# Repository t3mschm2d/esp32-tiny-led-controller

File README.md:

# ESP32-Tiny-LED-Controller

## Overview

The main goal of this project is to develop an OpenHardware board for controlling digital LED strips. The control shall be done via [Homeassistant](https://www.home-assistant.io) and [esphome](https://esphome.io).The PCB is based around an [ESP32-U4WDH](https://www.espressif.com/sites/default/files/documentation/esp32_datasheet_en.pdf) microcontroller and includes the following features: 

- 2,4GHz antenna for WLAN / Bluetooth 
- 5 pin screw terminal for external power and the LED-strip 
- USB-C connector
- USB-to-UART converter
- JST PH-S4B for connecting external sensors 

## ToDos

This PCB is a work in progress. The latest design is not tested and verified.

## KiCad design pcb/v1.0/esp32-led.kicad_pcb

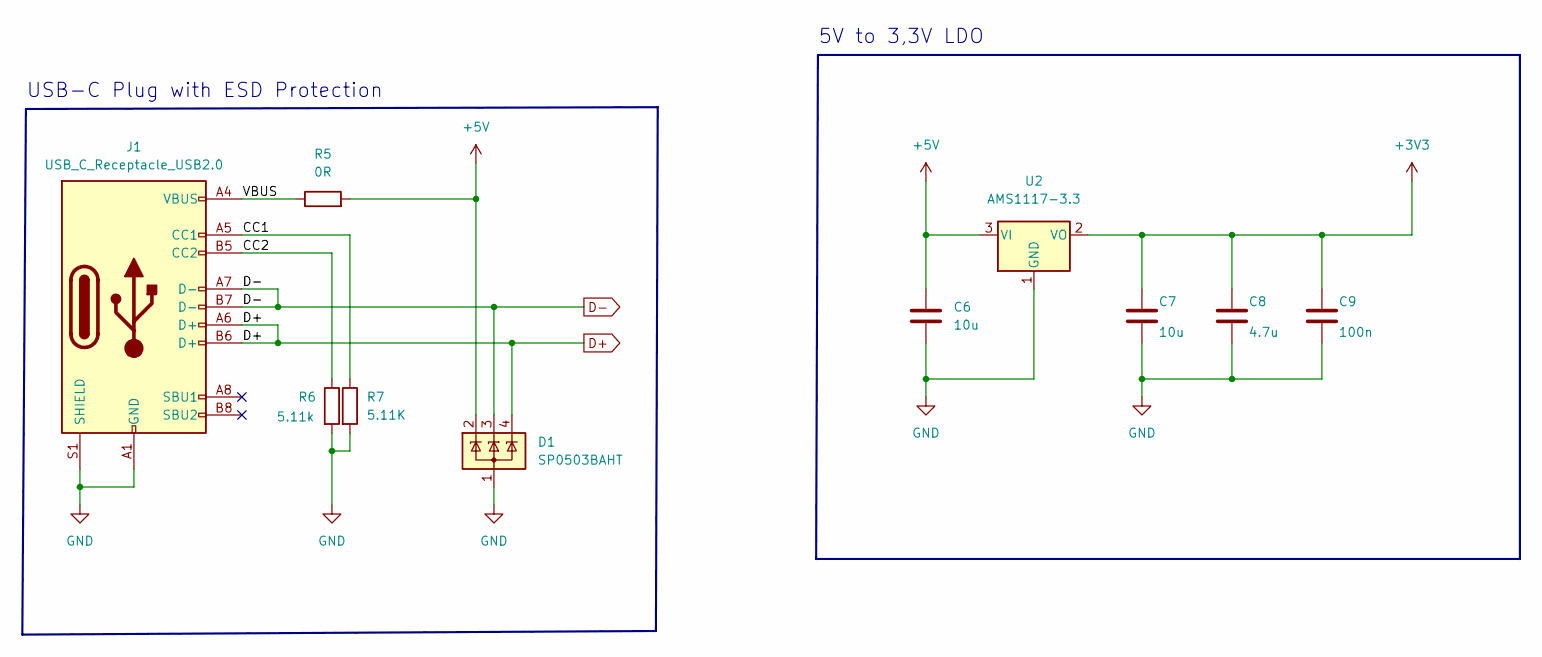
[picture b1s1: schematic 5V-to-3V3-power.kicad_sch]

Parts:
C6: 10u; C_0603_1608Metric
C7: 10u; C_0402_1005Metric
C8: 4.7u; C_0402_1005Metric
C9: 100n; C_0402_1005Metric
D1: SP0503BAHT; SOT-143
J1: USB_C_Receptacle_USB2.0; USB_C_Receptacle_JAE_DX07S016JA1R1500
R5: 0R; R_0805_2012Metric_Pad1.20x1.40mm_HandSolder
R6: 5.11k; R_0402_1005Metric
R7: 5.11K; R_0402_1005Metric
U2: AMS1117-3.3; SOT-223-3_TabPin2

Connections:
+3V3: C7.1, C8.1, C9.1, U2.2 (VO); also elsewhere on the board
+5V: C6.1, D1.2 (K), R5.2, U2.3 (VI); also elsewhere on the board
/5V to 3.3V Power/CC1: J1.A5 (CC1), R7.1
/5V to 3.3V Power/CC2: J1.B5 (CC2), R6.1
/5V to 3.3V Power/VBUS: J1.A4 (VBUS), J1.A9 (VBUS), J1.B4 (VBUS), J1.B9 (VBUS), R5.1
D+: D1.4 (K), J1.A6 (D+), J1.B6 (D+); also elsewhere on the board
D-: D1.3 (K), J1.A7 (D-), J1.B7 (D-); also elsewhere on the board
GND: C6.2, C7.2, C8.2, C9.2, D1.1 (A), J1.A1 (GND), J1.A12 (GND), J1.B1 (GND), J1.B12 (GND), J1.S1 (SHIELD), R6.2, R7.2, U2.1 (GND); also elsewhere on the board

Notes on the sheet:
5V to 3,3V LDO
USB-C Plug with ESD Protection

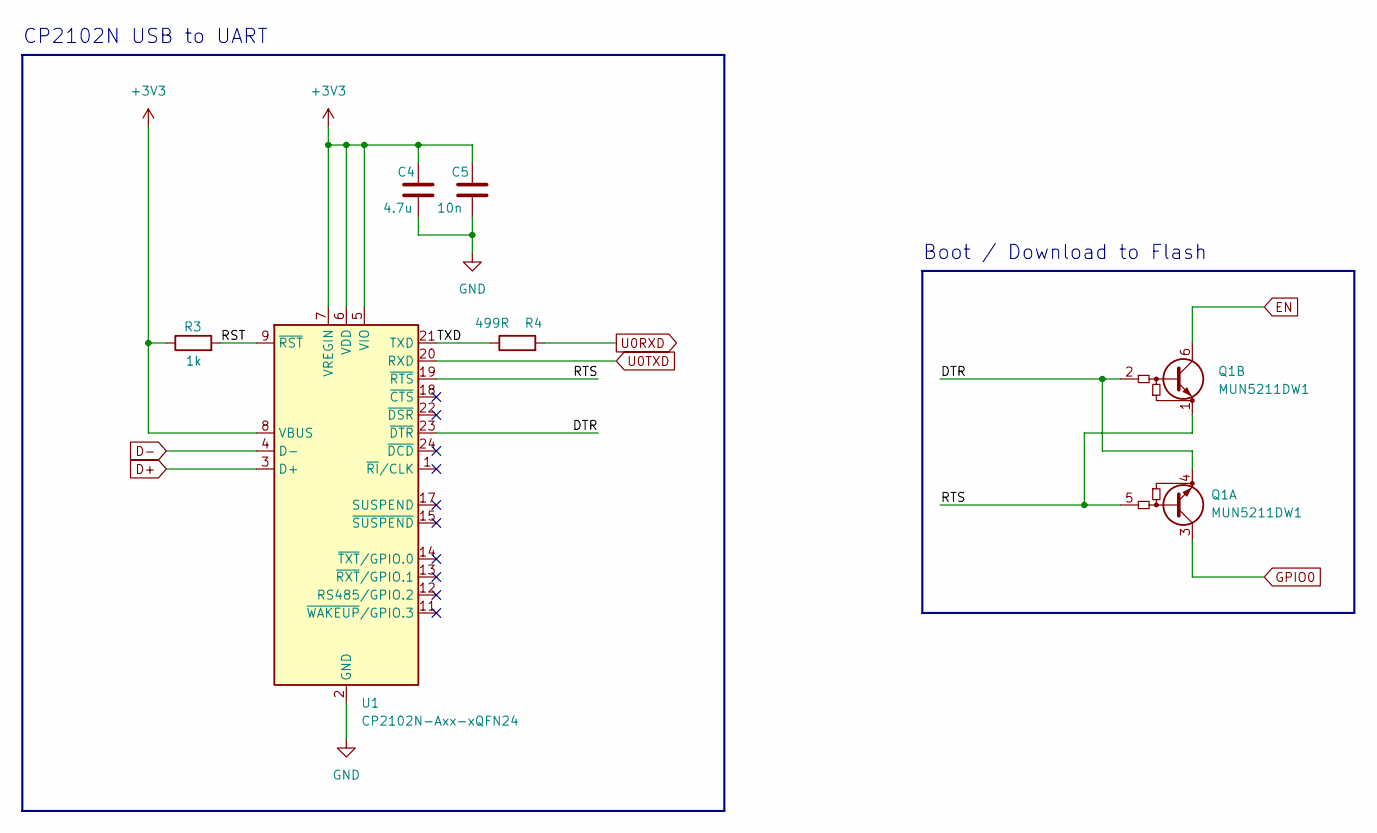
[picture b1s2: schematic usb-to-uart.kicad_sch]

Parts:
C4: 4.7u; C_0402_1005Metric
C5: 10n; C_0402_1005Metric
Q1: MUN5211DW1; SOT-363_SC-70-6
R3: 1k; R_0402_1005Metric
R4: 499R; R_0402_1005Metric
U1: CP2102N-Axx-xQFN24; QFN-24-1EP_4x4mm_P0.5mm_EP2.6x2.6mm

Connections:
+3V3: C4.1, C5.1, R3.1, U1.5 (VIO), U1.6 (VDD), U1.7 (VREGIN), U1.8 (VBUS); also elsewhere on the board
/USB to UART /DTR: Q1.2 (B2), Q1.4 (E1), U1.23 (~DTR)
/USB to UART /RST: R3.2, U1.9 (~RST)
/USB to UART /RTS: Q1.1 (E2), Q1.5 (B1), U1.19 (~RTS)
/USB to UART /TXD: R4.1, U1.21 (TXD)
D+: U1.3 (D+); also elsewhere on the board
D-: U1.4 (D-); also elsewhere on the board
EN: Q1.6 (C2); also elsewhere on the board
GND: C4.2, C5.2, U1.2 (GND), U1.25 (GND); also elsewhere on the board
GPIO0: Q1.3 (C1); also elsewhere on the board
U0RXD: R4.2; also elsewhere on the board
U0TXD: U1.20 (RXD); also elsewhere on the board

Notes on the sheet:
CP2102N USB to UART
Boot / Download to Flash

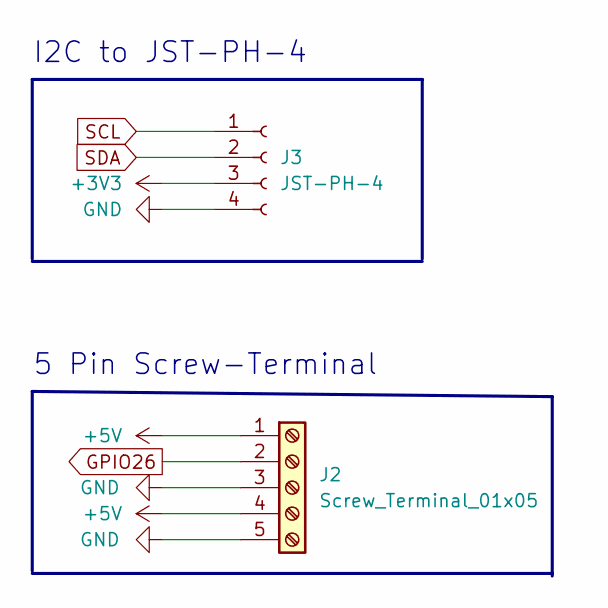
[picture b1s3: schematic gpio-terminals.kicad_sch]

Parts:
J2: Screw_Terminal_01x05; TerminalBlock_Phoenix_MKDS-1,5-5-5.08_1x05_P5.08mm_Horizont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
J3: JST-PH-4; JST_PH_S4B-PH-SM4-TB_1x04-1MP_P2.00mm_Horizontal

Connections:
+3V3: J3.3; also elsewhere on the board
+5V: J2.1, J2.4; also elsewhere on the board
GND: J2.3, J2.5, J3.4; also elsewhere on the board
GPIO26: J2.2; also elsewhere on the board
SCL: J3.1; also elsewhere on the board
SDA: J3.2; also elsewhere on the board

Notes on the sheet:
I2C to JST-PH-4
5 Pin Screw-Terminal

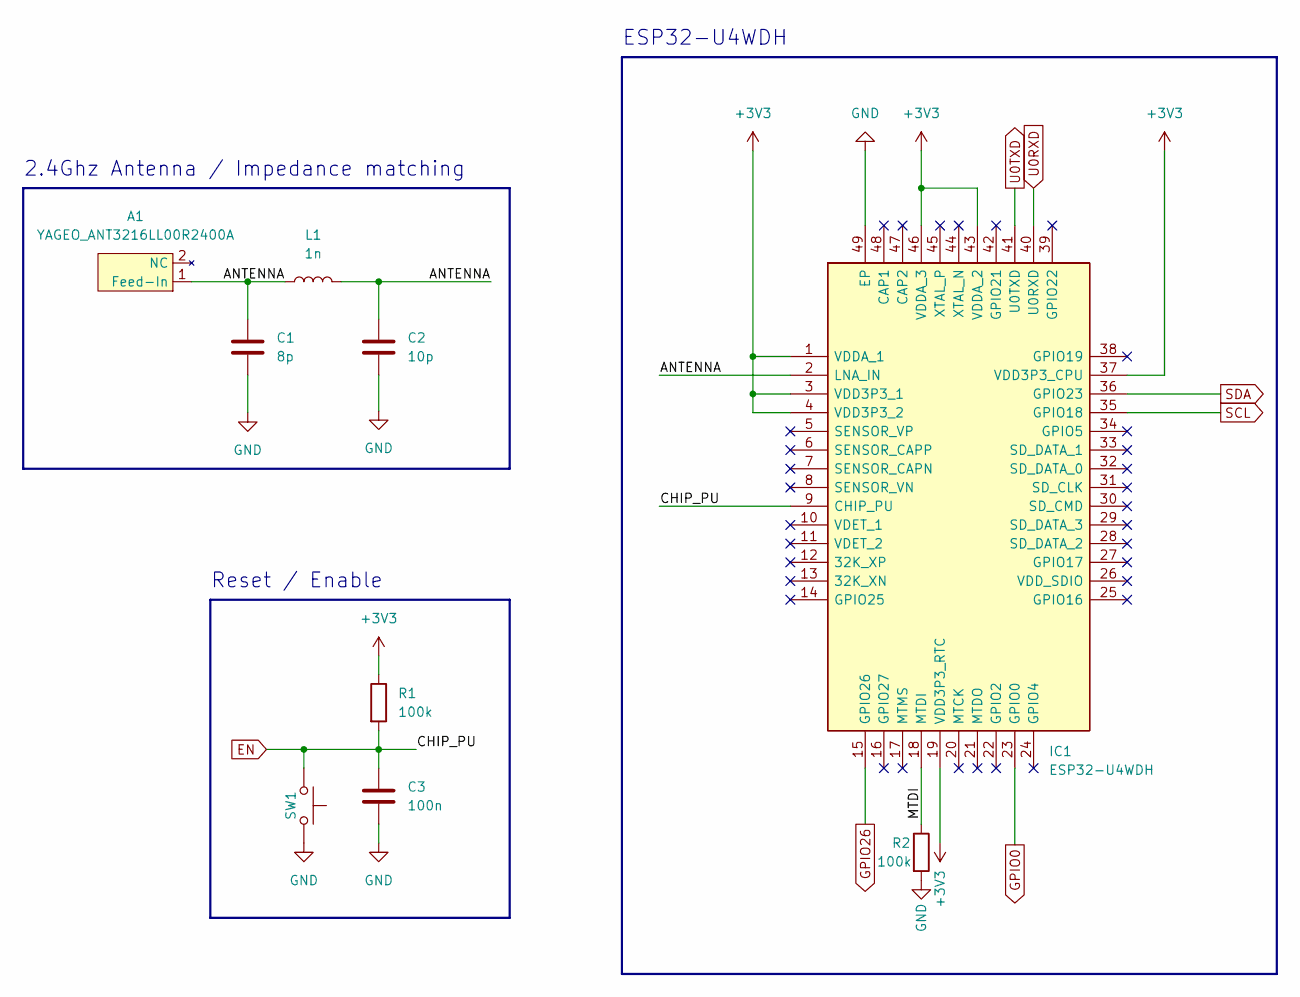
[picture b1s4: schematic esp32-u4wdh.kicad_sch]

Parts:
A1: YAGEO_ANT3216LL00R2400A
C1: 8p; C_0402_1005Metric
C2: 10p; C_0402_1005Metric
C3: 100n; C_0402_1005Metric
IC1: ESP32-U4WDH; QFN35P500X500X90-49N-D; Mouser Part Number 356-ESP32-U4WDH
L1: 1n; L_0402_1005Metric
R1, R2: 100k; R_0402_1005Metric
SW1: SW_Push; SW_SPST_B3U-1000P

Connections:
+3V3: IC1.1 (VDDA_1), IC1.3 (VDD3P3_1), IC1.4 (VDD3P3_2), IC1.19 (VDD3P3_RTC), IC1.37 (VDD3P3_CPU), IC1.43 (VDDA_2), IC1.46 (VDDA_3), R1.1; also elsewhere on the board
/ESP32-U4WDH/ANTENNA: A1.1 (Feed-In), C1.1, C2.1, IC1.2 (LNA_IN), L1.1, L1.2
/ESP32-U4WDH/MTDI: IC1.18 (MTDI), R2.1
EN: C3.1, IC1.9 (CHIP_PU), R1.2, SW1.1; also elsewhere on the board
GND: C1.2, C2.2, C3.2, IC1.49 (EP), R2.2, SW1.2; also elsewhere on the board
GPIO0: IC1.23 (GPIO0); also elsewhere on the board
GPIO26: IC1.15 (GPIO26); also elsewhere on the board
SCL: IC1.35 (GPIO18); also elsewhere on the board
SDA: IC1.36 (GPIO23); also elsewhere on the board
U0RXD: IC1.40 (U0RXD); also elsewhere on the board
U0TXD: IC1.41 (U0TXD); also elsewhere on the board

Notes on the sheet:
ESP32-U4WDH
Reset / Enable
2.4Ghz Antenna / Impedance matching

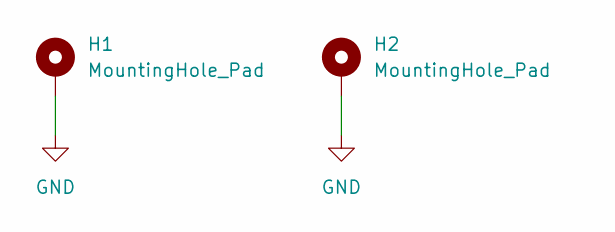
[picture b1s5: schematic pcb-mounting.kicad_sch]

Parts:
H1, H2: MountingHole_Pad; MountingHole_2.2mm_M2_Pad

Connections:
GND: H1.1, H2.1; also elsewhere on the board

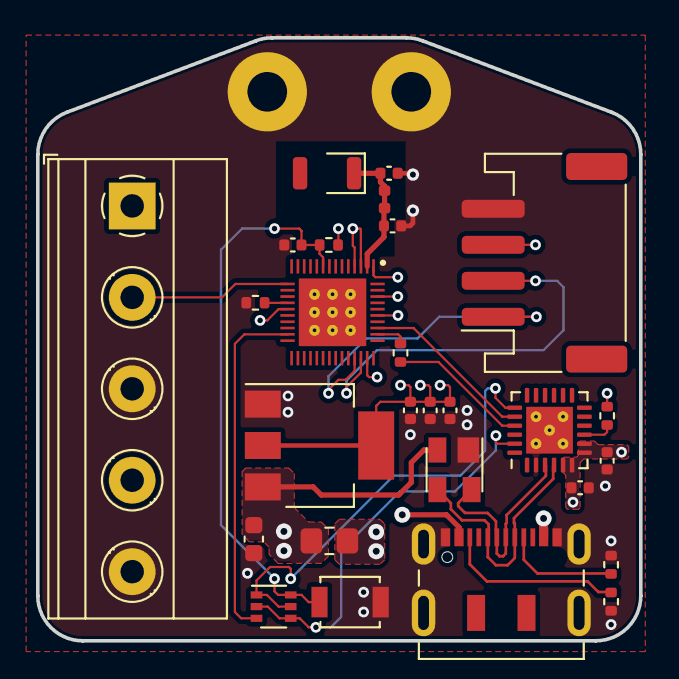
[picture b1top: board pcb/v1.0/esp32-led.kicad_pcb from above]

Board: 4 copper layers, 33.5 x 33.5 mm, 29 parts (0 on the bottom side), 21 nets.

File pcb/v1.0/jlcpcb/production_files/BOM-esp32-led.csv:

Comment,Designator,Footprint,LCSC
5.11k,"R6,R7",R_0402_1005Metric,C103084
10p,C2,C_0402_1005Metric,C106199
100k,"R1,R2",R_0402_1005Metric,C106234
1k,R3,R_0402_1005Metric,C106235
100n,"C3,C9",C_0402_1005Metric,C131394
499R,R4,R_0402_1005Metric,C137970
0R,R5,R_0805_2012Metric_Pad1.20x1.40mm_HandSolder,C169855
SW_Push,SW1,SW_SPST_B3U-1000P,C231329
1n,L1,L_0402_1005Metric,C237608
JST-PH-4,J3,JST_PH_S4B-PH-SM4-TB_1x04-1MP_P2.00mm_Horizontal,C265102
10n,C5,C_0402_1005Metric,C272878
YAGEO_ANT3216LL00R2400A,A1,YAGEO_ANT3216LL00R2400A,C293767
ESP32-U4WDH,IC1,QFN35P500X500X90-49N-D,C3013932
SP0503BAHT,D1,SOT-143,C3040626
8p,C1,C_0402_1005Metric,C342939
MUN5211DW1,Q1,SOT-363_SC-70-6,C463894
AMS1117-3.3,U2,SOT-223-3_TabPin2,C6186
10u,C7,C_0402_1005Metric,C76991
4.7u,"C4,C8",C_0402_1005Metric,C82453
10u,C6,C_0603_1608Metric,C85713
CP2102N-Axx-xQFN24,U1,QFN-24-1EP_4x4mm_P0.5mm_EP2.6x2.6mm,C969151

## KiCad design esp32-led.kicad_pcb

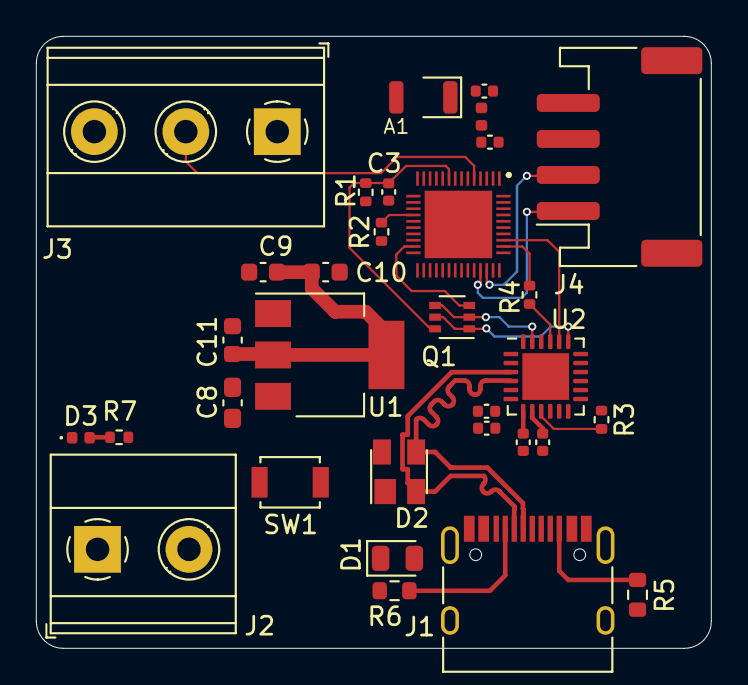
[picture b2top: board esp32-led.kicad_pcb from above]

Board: 4 copper layers, 37.5 x 34.0 mm, 32 parts (0 on the bottom side), 23 nets.

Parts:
A1: YAGEO_ANT3216LL00R2300A
C1: 8pF; C_0402_1005Metric
C2: 10pF; C_0402_1005Metric
C3: 10uF; C_0402_1005Metric
C4, C5: 4.7uF; C_0402_1005Metric
C6, C7: 0.1uF; C_0402_1005Metric
C8: 10uF; C_0603_1608Metric_Pad1.08x0.95mm_HandSolder
C9: 10uF; C_0603_1608Metric
C10: 10uF/6.3V(10%); C_0603_1608Metric
C11: 0.1uF/25V(10%); C_0603_1608Metric
D1: D_Schottky; D_0805_2012Metric
D2: SP0503BAHT; SOT-143
D3: LED; LED_0402_1005Metric
IC1: ESP32-U4WDH; QFN35P500X500X90-49N-D
J1: USB_C_Receptacle_USB2.0; USB_C_Receptacle_HRO_TYPE-C-31-M-12
J2: Screw_Terminal_01x02; TerminalBlock_Phoenix_MKDS-1,5-2-5.08_1x02_P5.08mm_Horizont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
J3: Screw_Terminal_01x03; TerminalBlock_Phoenix_MKDS-1,5-3-5.08_1x03_P5.08mm_Horizont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
J4: JST-PH-4; JST_PH_S4B-PH-SM4-TB_1x04-1MP_P2.00mm_Horizontal
L1: 1nH; L_0402_1005Metric
Q1: MUN5211DW1; SOT-363_SC-70-6
R1: 10K; R_0402_1005Metric
R2: 10K(5%); R_0402_1005Metric
R3: 2K; R_0402_1005Metric
R4: 499R(1%); R_0402_1005Metric
R5, R6: 5.11K; R_0603_1608Metric
R7: 200; R_0402_1005Metric
SW1: SW_Push; SW_SPST_B3U-1000P
U1: AMS1117-3.3; SOT-223-3_TabPin2
U2: CP2102N-Axx-xQFN24; QFN-24-1EP_4x4mm_P0.5mm_EP2.6x2.6mm

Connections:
+3.3VA: C4.1, C5.1, C6.1, C7.1, C9.1, C10.1, C11.1, IC1.1 (VDDA_1), IC1.3 (VDD3P3_1), IC1.4 (VDD3P3_2), IC1.19 (VDD3P3_RTC), IC1.37 (VDD3P3_CPU), IC1.43 (VDDA_2), IC1.46 (VDDA_3), J4.3, R1.1, R3.1, U1.2 (VO), U2.5 (VIO), U2.6 (VDD), U2.7 (VREGIN), U2.8 (VBUS)
/ESP32-U4WDH/ANTENNA: C2.1, IC1.2 (LNA_IN), L1.2
/USB to UART /DTR: Q1.2 (B2), Q1.4 (E1), U2.23 (~DTR)
/USB to UART /RTS: Q1.1 (E2), Q1.5 (B1), U2.19 (~RTS)
D+: D2.2 (K), J1.A7 (D-), J1.B7 (D-), U2.3 (D+)
D-: D2.3 (K), J1.A6 (D+), J1.B6 (D+), U2.4 (D-)
EN: C3.1, IC1.9 (CHIP_PU), Q1.6 (C2), R1.2, SW1.1
GND: C1.2, C2.2, C3.2, C4.2, C5.2, C6.2, C7.2, C8.2, C9.2, C10.2, C11.2, D2.1 (A), D3.1 (K), IC1.49 (EP), J1.A1 (GND), J1.A12 (GND), J1.B1 (GND), J1.B12 (GND), J1.S1 (SHIELD), J2.1, J3.3, J4.4, R2.2, R5.2, R6.2, SW1.2, U1.1 (GND), U2.2 (GND), U2.25 (GND)
GPIO0: IC1.23 (GPIO0), Q1.3 (C1)
GPIO36: IC1.5 (SENSOR_VP), J3.2
HIGH_POWER_5V: C8.1, D1.1 (K), D2.4 (K), J2.2, J3.1, R7.1, U1.3 (VI)
unnamed: A1.1 (Feed-In), C1.1, L1.1
unnamed: D1.2 (A), J1.A4 (VBUS), J1.A9 (VBUS), J1.B4 (VBUS), J1.B9 (VBUS)
unnamed: D3.2 (A), R7.2
unnamed: IC1.18 (MTDI), R2.1
unnamed: J1.A5 (CC1), R6.1
unnamed: J1.B5 (CC2), R5.1
unnamed: R3.2, U2.9 (~RST)
unnamed: R4.1, U2.21 (TXD)
SCL: IC1.35 (GPIO18), J4.1
SDA: IC1.36 (GPIO23), J4.2
U0RXD: IC1.40 (U0RXD), R4.2
U0TXD: IC1.41 (U0TXD), U2.20 (RXD)

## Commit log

2022-11-18 ADD initial schematic and first layout plans
2022-11-22 ADD placement and rounting for ESP32-LED Driver
2022-11-23 ADD subfolder for pcb
2022-11-23 ADD Readme.md
2022-11-23 ADD .gitignore
2022-11-23 REF .gitignore
2022-11-23 ADD dropped .gitignore files
2022-11-23 ADD Read Me
2022-11-26 Add board view to README
2022-12-01 ADD 3D Models for all footprints, export new PCB Image and remove D1 for R8 with 0R (Jumper R)
2022-12-02 ADD new picture, and propper GND plane on top layer
2022-12-02 UPDATE thermal relief pads for ESP, USB-UART
2022-12-05 REF PCB Layout, Switch to new USB-C Receptable
2022-12-05 REF TVS-Diode Layout
2022-12-05 REF img
2023-01-29 ADD new READ.me
